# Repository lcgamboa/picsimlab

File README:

PICsimLab - PIC Simulator Laboratory

PicsimLab is a realtime emulator of development boards with integrated MPLABX debugger.
PicsimLab supports picsim  microcontrollers PIC16F84A, 16F628A, 16F648A, 16F777, 16F777, 16F877A, 18F452, 18F4520, 18F4550, 18F4620 and ATMEGA328P.

Requirements:

wxwidget 	- For graphic suport		   http://www.wxwidgets.org
picsim          - PIC simulator                    https://github.com/lcgamboa/picsim or http://sourceforge.net/projects/picsim 
lxrad           - Graphic library                  https://github.com/lcgamboa/lxrad or http://sourceforge.net/projects/lxrad
simavr		- AVR simulator                    https://github.com/buserror/simavr

Utils:

com0com		- For serial emulation in windows  http://com0com.sourceforge.net/ 
tty0tty 	- For serial emulation in linux    https://github.com/lcgamboa/tty0tty or http://tty0tty.sourceforge.net/

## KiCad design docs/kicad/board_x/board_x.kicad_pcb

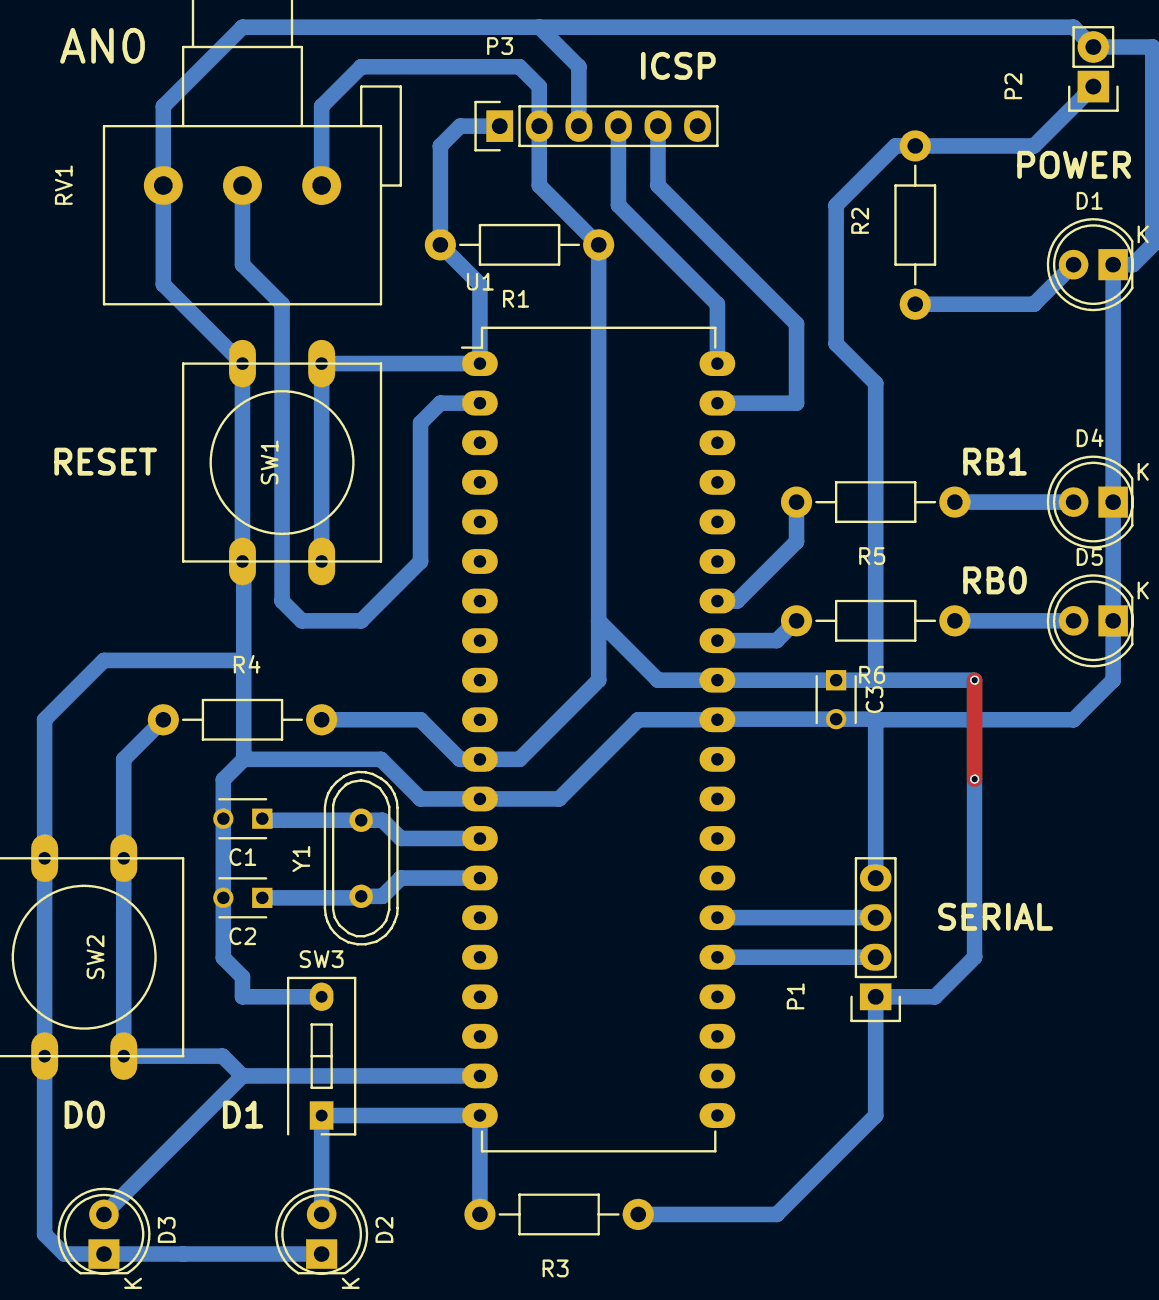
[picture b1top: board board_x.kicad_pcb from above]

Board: 2 copper layers, 23 parts (0 on the bottom side), 17 nets.

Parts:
C1, C2: 15pF; C_Disc_D3_P2.5
C3: 100nF; C_Disc_D3_P2.5
D1: BLUE; LED-5MM
D2: YELLOW; LED-5MM
D3: WHITE; LED-5MM
D4: RED; LED-5MM
D5: GREEN; LED-5MM
P1: Serial; Socket_Strip_Straight_1x04
P2: POWER; Socket_Strip_Straight_1x02
P3: ICSP; Socket_Strip_Straight_1x06
R1: 10k; Resistor_Horizontal_RM10mm
R2, R3, R4, R5, R6: 1k; Resistor_Horizontal_RM10mm
RV1: 10K; Potentiometer_Alps-RK163-single_15mm
SW1: RESET; SW_PUSH-12mm
SW2: SW_PUSH; SW_PUSH-12mm
SW3: SPST; SW_DIP_x1_Slide
U1: PIC18F4550; DIP-40_W15.24mm_LongPads
Y1: 8MHz; Crystal_HC49-U_Vertical

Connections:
+5V: C3.1, P1.1, P2.1, P3.2, R1.1, R2.2, R3.1, R4.2, RV1.1, U1.11, U1.32
GND: C1.2, C2.2, C3.2, D1.1, D2.1, D3.1, D4.1, D5.1, P1.4, P2.2, P3.3, RV1.3, SW1.1, SW2.2, SW3.2, U1.12, U1.31
unnamed: C1.1, U1.13, Y1.2
unnamed: C2.1, U1.14, Y1.1
unnamed: D1.2, R2.1
unnamed: D2.2, R3.2, SW3.1, U1.20
unnamed: D3.2, R4.1, SW2.1, U1.19
unnamed: D4.2, R5.1
unnamed: D5.2, R6.1
unnamed: P1.2, U1.25
unnamed: P1.3, U1.26
unnamed: P3.1, R1.2, SW1.2, U1.1
unnamed: P3.4, U1.40
unnamed: P3.5, U1.39
unnamed: R5.2, U1.34
unnamed: R6.2, U1.33
unnamed: RV1.2, U1.2

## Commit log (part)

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2022-10-04 fix: Use correct system text color to work on dark mode !minor
2022-10-04 chg: Support to save board options of each instance !minor
2022-10-09 chg: Update rcontrol to use input/output ids array in boards !minor
2022-10-14 chg: Code refactoring for future support of building PICSimLab as a library. !minor
2022-10-22 chg: Fix experimental boards code refactor !minor
2022-10-22 Fix: Add support to windows serial ports greater than COM9 in qemu backend simulator.
2022-10-23 new: New board Arduino Nano added.
2022-10-26 chg: Remove image background to use transparency !minor
2022-10-29 chg: Error detection method changed. !minor
2022-10-30 fix: Fix stdout log messages redirection !minor
2022-11-06 fix: Fix PinViewer to work with Wayland (Linux) !minor
2022-11-19 chg: Code cleanup !minor
2022-11-26 new: Support to I2C in qemu-stm32 added
2022-11-27 chg: Add instance numbers to windows title bars
2022-12-11 chg: Parts code refactor mouse events and draw !minor
2022-12-24 new: Support to SPI in bmp280 sensor added
2022-12-24 fix: Fix code typo !minor
2022-12-24 fix: Fix mingw32 build !minor
2023-01-03 new: New tests for I2C and SPI PIC18F support !minor
2023-01-03 new: New part ADXL345 Accelerometer
2023-01-05 fix: Fix SPI CIPO signal phase !minor
2023-01-10 new: Support to use Virtual Terminal part with rcontrol interface
2023-01-13 new: Support to use UART pins with qemu ESP32 and STM32 added
2023-01-13 chg: Support to save the state of VCD Dump !minor
2023-01-14 fix: Disable RegisterRemoteControl when using Emscripten !minor
2023-01-14 chg: Remove the use of virtual serial port on tests !minor
2023-01-15 new: Support to PIC16F886 and PIC18F28K80 added to Breadboard board
2023-01-17 fix: Fix board menu freeze !minor
2023-01-20 fix: Fix stm32 qemu afio map use in PICSimLab !minor
2023-01-20 new: Version 0.8.12
2023-02-05 fix: Add support to use atmega2560 four UARTs
2023-02-09 chg: Add the "Load Board Demo" menu option and automatic demo load on board first use
2023-02-11 Add .gitignore to prevent accidentally committing the build folder
2023-02-11 new: Support to enable/disable reset by DTR/RTS serial signals
2023-02-11 fix: Fix the support to enable/disable reset by DTR/RTS in Devkitc Board !minor
2023-02-13 fix: Fix build script dir output !minor
2023-02-15 new: Support to save Board and Oscilloscope windows postions and options per board
2023-02-15 new: Support to PIC16F1829 added to Breadboard board
2023-02-18 chg: Disable rcontrol message when rcontrol is disabled !minor
2023-02-27 fix: Fix crash on Linux when board is changed with oscilloscope window open. !minor
2023-03-06 new: Support to PIC16F1516 and PIC1824Q10 added to Breadboard board
2023-03-11 new: Support to PIC16F1947 added to Breadboard board
2023-03-11 chg: Update debian package version !minor
2023-03-27 chg: Update Makefiles to work with lunasvg new version !minor
2023-04-06 fix: Fix Arduino Nano board power and uart pins
2023-04-06 chg: Icons updated
2023-04-06 chg: Update flatpak to use last lunasvg version !minor
2023-04-08 Add *.o and other files generated after compiling to gitignore
2023-04-12 chg: Update Readme links !minor
2023-04-16 fix: Fix TextBox init sporadic error messages.
2023-04-16 chg: Update spi test !minor
2023-04-16 chg: Update flatpak to use new qemu. !minor
2023-04-27 chg: Code refactoring to support change simulator FPS !minor
2023-04-27 fix: Fix pin initial value used by LEDs and 7 seg. displays
2023-04-28 fix: Update experimental boards to build !minor
2023-04-29 new: Add support to syncronize Remote TCP simulation
2023-05-01 fix: Fix missing uart init !minor
2023-05-02 fix: Fix RemoteTCP board SPI pin name !minor
2023-05-13 chg: Change input_ids and output_ids to be initialized without null !minor
2023-05-20 new: New part NTC temperature sensor.
2023-05-22 chg: Add stack trace to log when PICSimLab crash
2023-05-22 chg: Fix code to work with emscripten !minor
2023-05-28 chg: scripts updated !minor
2023-05-29 fix: Fix serial port baudrate calculation.
2023-06-02 fix: Fix crash in rcontrol when use PinViewer pin toggle on qemu based boards
2023-06-02 fix: Fix RemoteTcp board spi !minor
2023-06-04 chg: Add support to biybang_spi read values bigger than eight !minor
2023-06-11 Update simulated PQDB board to work like the real one, added support for PIC18F4550 and PIC18F4620.
2023-06-17 new: Add support to IO virtual term part autodetect uart pins
2023-06-17 new: Add support to use efuse file with ESP32 qemu based boards.
2023-06-25 chg: Replace ESP32-C3-DevKitC-02 board PNG image for SVG !minor
2023-07-02 new: Move RemoteTCP board from experimental to stable version.
2023-07-08 chg: Add Remote TCP board suport to use demostration project. !minor
2023-07-08 new: Add suport to ESP32-C3 to use efuse file.
2023-07-09 new: Add support to Text Box part open external URLs on click.
2023-07-15 chg: Demonstration projects updated !minor
2023-07-15 fix: Add line break in Virtual Term to avoid UI freezing
2023-07-15 fix: Fix button read after pin mode set to input in McLab2 board
2023-07-29 new: Version 0.9.0 !minor
2023-07-29 chg: Readme updated !minor
2023-08-26 chg: Add support to use custom size of flash memory in bsim_qemu !minor
2023-08-26 chg: Add support to change ambient temperature and LM35 voltage offset in TempSys spare part.
2023-08-29 chg: Scripts updated and max flash file size fixed for qemu
2023-09-02 fix: Fix redirection error when home dir don´t exists !minor
2023-09-03 chg: Draw the spare part before clicking in the window when a new part is added
2023-09-04 fix: Fix Arduino Uno board missing spare parts when open workspace files
2023-09-08 fix: Fix invalid serial handle in Windows
2023-09-09 fix: Fix SDCard spare parts CIPO signal.
2023-09-24 new: SD card initial support to CRC16 on (ESP32 compatibility).
2023-09-25 new: SD card support to CRC16 on write block and CRC7 on commands
2023-10-01 new: Add suport to ESP32 LEDC (PWM output)
2023-10-07 chg: Rename speed label from Clk to IO in qemu boards
2023-10-12 chg: Add id to wifi and ethernet interfaces in Qemu based boards !minor
2023-10-15 chg: Change vterm font to monospaced
2023-10-29 fix: Fix invalid serial read on qemu based boards.
2023-11-12 chg: Add support to save Vterm window size.
2023-12-02 new: Add WIFI support to ESP32C3 and ESP-NOW protocol
2023-12-10 Version 0.9.1
2023-12-21 new: Add support to PWM outputs for ESP32C3 and STM32 boards
2023-12-26 fix: Fix ESP32C3 tests to work on windows !minor
2024-01-06 new: Add support to use analog values in gpboard (gpsim backend)
2024-01-08 chg: Code refactor to remove statusbar reference !minor
2024-01-08 chg: Code refactor remove ::FromAscii !minor
2024-01-11 chg: Code refactor replace lxString for std::string !minor
2024-01-13 chg: Code refactor - Moving menu stuff out library !minor
2024-01-14 chg: Code refactor - Add callbacks to isolate gui access. !minor
2024-01-19 chg: Code refactor - Add callbacks for image loading and creation !minor
2024-01-26 chg: Code refactor - prepare to use abstract canvas !minor
2024-01-29 chg: Code refactor - Remove direct use of lxBimap !minor
2024-01-29 chg: Code refactor - Remove LoadImage and CreateImage !minor
2024-02-01 chg: Code refactor - Fix Spin and Combo events !minor
2024-02-04 chg: Code refactor - Fix Windows freezing !minor
2024-02-10 chg: Code refactor - Add SystemCmd bridge !minor
2024-02-10 chg: Code refactor - replace uint by unsigned int !minor
2024-02-15 chg: fix basename SystemCmd !minor
2024-03-02 fix: Fix support to multi byte char in command line file name
2024-03-24 new: Support to PIC18F67J60 added to Breadboard board
2024-04-06 fix: Fix gpboard simulation clock speed.
2024-04-06 fix: Fix gpboard configuration bits dump for PIC18F.
2024-04-13 new: Increase oscilloscope time scale up to 1s/div.
2024-04-14 new: New part \"Logic Block\" with logic functions: Not, Buffer, And, Nand, Or, Nor, Xor and Xnor.
2024-04-15 fix: Fix Spareparts Prop window position on windows !minor
2024-04-15 chg: Add board method MGetClocksPerInstructions. !minor
2024-05-26 chg: Makefile updated to build in any plataform !minor
2024-06-15 new: New spare part MCP23017 I2C IO expander
2024-06-15 fix: Fix RTC DS1307 support to 12h mode
2024-06-15 fix: Fix spare parts properties window position
2024-06-22 new: Add a new picsimlab_tool command line tool to upload firmware direct to PICSimLab (from platformio).
2024-06-24 chg: Add suport to set PWM frequency in bitbang_pwm (LEDC for ESP32, ESP32C3)
2024-06-27 Update README.md
    Removed extra "The" from the docs.
2024-06-30 chg: Add support to set baud rate in bitbang_uart (ESP32 and ESP32C3)
2024-07-07 chg: Add support to set baud rate in bitbang_uart (STM32 boards)
2024-07-08 chg: Build scritpts updated !minor
2024-07-20 chg: On fails make backup and load demonstrantion workspace to recover
2024-07-20 chg: Build scripts updated. !minor
2024-07-21 fix: Fix the timestamp when save backup !minor
2024-08-03 chg: Adds support for showing in the status bar when waiting for GDB connection.
2024-08-18 fix: Fix BluePill Board onboard LED polarity.
2024-10-05 new: Version 0.9.2 realease!
2024-10-05 chg: github actions updated
2024-11-30 fix: Fix ili9341 with "spi+touch" crashes. Thanks to m-meltner https://github.com/lcgamboa/picsimlab/issues/131
2024-11-30 new: New spare part VCD Dump Memory (RAM).
2025-03-04 chg: Support to 16 bit memory in VCD Dump Memory part added.
2025-03-04 chg: Github action updated to remove ubuntu-20.04 deprecated build !minor
2025-04-19 fix: Fix gpboard write to input pins bug
2025-04-19 chg: Code refactor to better isolate backend classes !minor
2025-08-10 fix: Add limits to print pins names. !minor
2025-10-18 fix: Fix LCD hd44780 and Virtual terminal to update on debug stepping
2025-12-09 fix: Fix IO Virtual terminal window controls response when one part deleted
2025-12-09 fix: Remove error log message when None HWSerial is selected
2025-12-14 fix: Fix the empty spare parts config in backup when errors are detected
2025-12-29 chg: VERSION date updated !minor
2025-12-30 chg: Add support to show messages when unknown opcodes are detected in PIC based boards.
2026-01-04 chg: Update build scripts !minor
2026-01-05 chg: Build scritps updated
2026-01-05 fix: Fix the error of using file paths with space in some spare parts
2026-02-25 fixed pinviewer not correctly displaying with highdpi font, by scaling verything depending on the font size and not hardcoded font size in pixels
2026-02-28 moved pin update before cpu update to have latest pin updated in spare parts
2026-03-04 fix led matrix not exposed to rcontrol and register pBoot to be able to set the gpio0 state
2026-03-07 removed tabs
2026-03-11 implemented qemu sim stop/start
2026-03-11 fixed compilation issues when building using non system dir (local build only)
2026-03-12 removed unneeded condition to pboard
2026-04-19 chg: Updated libcurl to use cacert.pem.
2026-04-19 new: New rcontrols commands sprdcfg and spwrcfg to configure spare parts
2026-05-03 fix: Fix number of fields of virtual terminal in .pcf files !minor
2026-05-10 chg: Updated to use qemu-esp32 0.9.2.
2026-05-17 chg: Update flatpak to use system version 24.08 !minor
2026-05-24 chg: More information has been added to the about and the update windows.
2026-05-24 chg: Install scripts updated. !minor
2026-05-31 Fix: Fixes crashes that occurred when using an oscilloscope on qemu-based boards in Windows.
2026-05-31 chg: Docs updated !minor
2026-06-07 new: New rcontrol commnads blist (supported boards list) and buclist (board supported microcontrollers list).
2026-06-07 new: New code generator Project Wizard module (Vscode+platformio Arduino Uno).
2026-06-13 new: The new Code menu, new option to load the active project and VScode auto detection.
2026-06-14 new: New support to boards Arduino Mega, Arduino Nano and Franzininho DIY on Project Wizard
2026-06-17 New: Add support to open existent code project on project wizard window
2026-06-17 chg: Remove picsimlab_tool first command line parameter.
2026-06-17 new: New rcontrol commands spshow, spdel, oscshow, oscmeasures, oscrdcfg and oscwrcdg
2026-06-21 chg: Change projects template to use picsimlab_tool.py
2026-06-28 chg: Modify command line to pass board or pzw file as first parameter.
